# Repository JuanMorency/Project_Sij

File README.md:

# Project_Sij
Complete 600 mm Frame Drone Electrical and Sotware Design using:

- Atmega2560
- MPU9255
- 4 channel RF receiver
- Flycopter 30A BH-heli motor controllers
- WS2812B LED strips
- Madgwick Sensor Fusion

PCB was designed using Eagle. 

Second iteration of the board with much more processing power for sensor fusion should be considered to continue this project

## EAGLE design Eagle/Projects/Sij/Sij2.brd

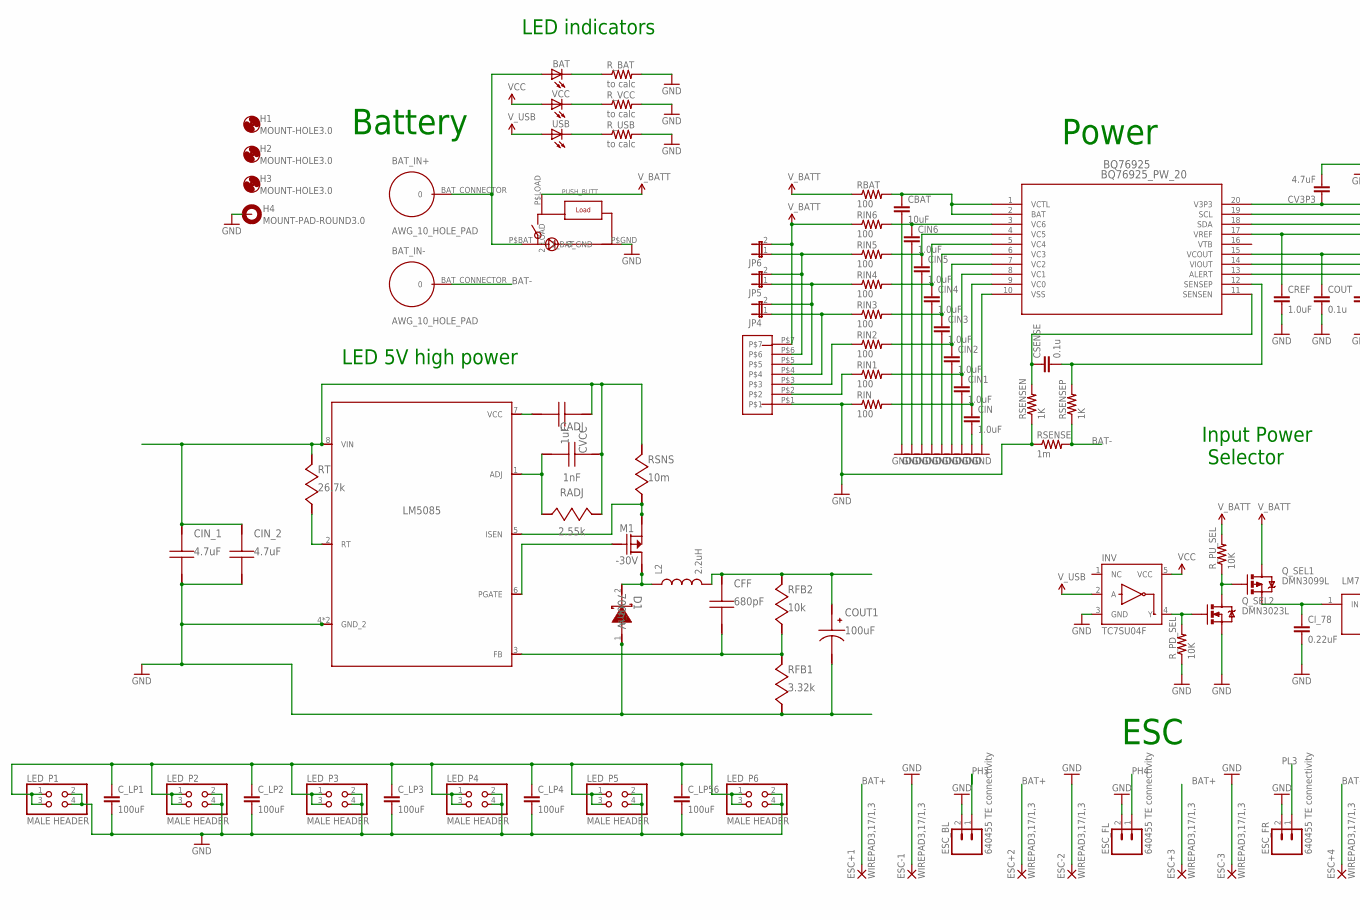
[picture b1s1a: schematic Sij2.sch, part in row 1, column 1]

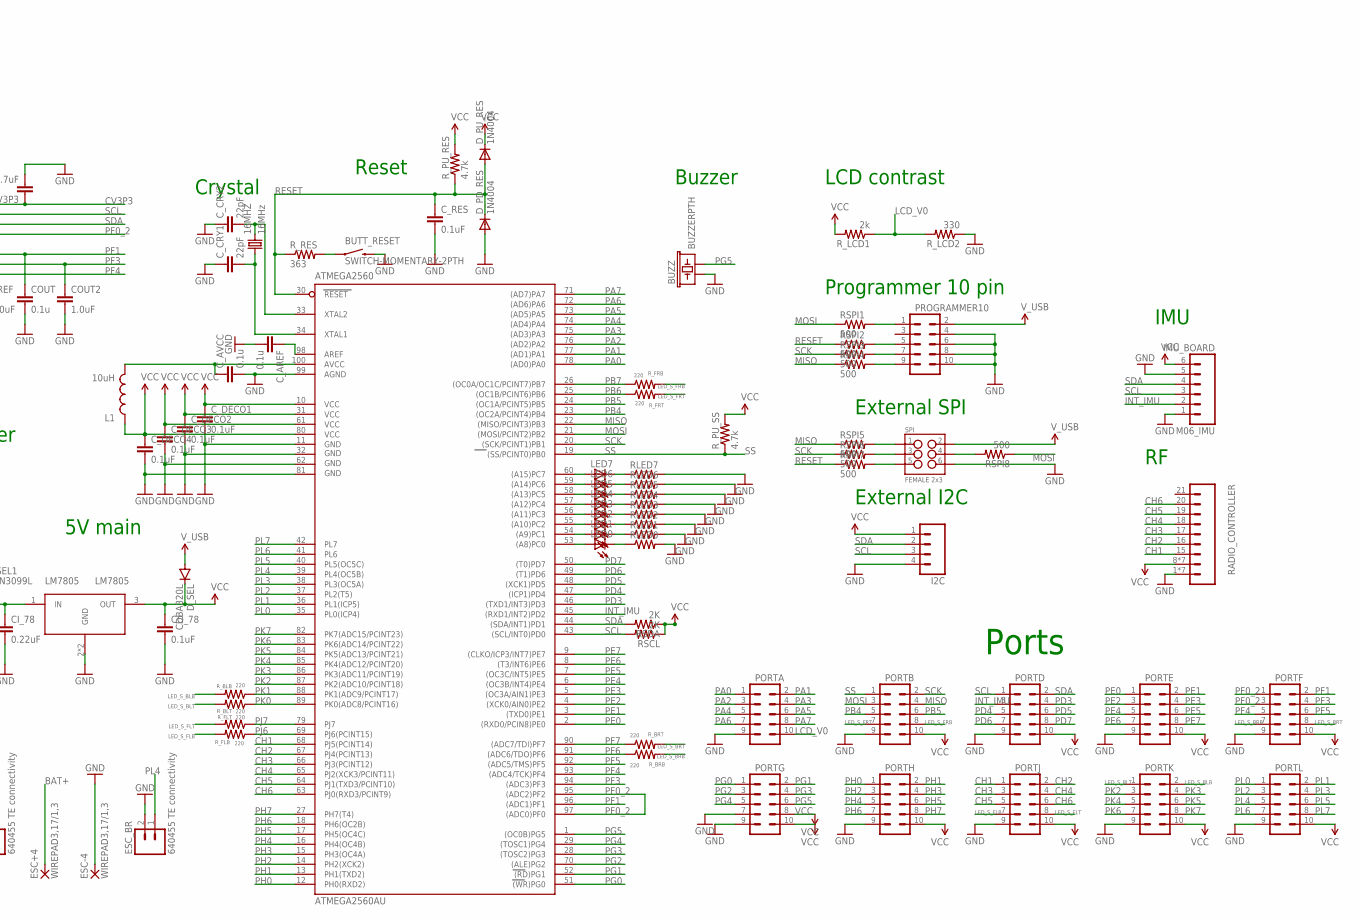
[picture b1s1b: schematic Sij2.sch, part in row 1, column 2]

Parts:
16MHZ: 16MHz; HC49US
ATMEGA2560: ATMEGA2560AU; TQFP100
BAT: LEDCHIPLED_0805; CHIPLED_0805
BAT-MONIT: 7_PIN_JST-XH
BAT_IN+: AWG_10_HOLE_PAD; AWG10_HOLE_PAD
BAT_IN-: AWG_10_HOLE_PAD; AWG10_HOLE_PAD
BQ76925: BQ76925_PW_20; PW20
BUTT_RESET: SWITCH-MOMENTARY-2PTH; TACTILE-PTH
BUZZ: BUZZERPTH; BUZZER-12MM
CADJ: 1nF; 0201
CBAT: 10uF; 0805
CFF: 680pF; 0603
CIN, CIN1, CIN2, CIN3, CIN4, CIN5, CIN6: 1.0uF; 0603-CAP
CIN_1, CIN_2: 4.7uF; 0805
CI_78: 0.22uF; 0603-CAP
COUT: 0.1u; 0603-CAP
COUT1: 100uF; CAPSMT_6_A09
COUT2: 1.0uF; 0603-CAP
CO_78: 0.1uF; 0603-CAP
CREF: 1.0uF; 0603-CAP
CSENSE: 0.1u; 0603-CAP
CV3P3: 4.7uF; 0603-CAP
CVCC: 1uF; 0603
C_AREF: 0.1u; 0603-CAP
C_AVCC: 0.1u; 0603-CAP
C_CRY1, C_CRY2: 22pF; 0603-CAP
C_DECO1, C_DECO2, C_DECO3, C_DECO4: 0.1uF; 0603-CAP
C_LP1, C_LP2, C_LP3, C_LP4, C_LP56: 100uF; 1206
C_RES: 0.1uF; 0603-CAP
D1: 700mV; DDPAK
D_PD_RES: 1N4004; DO41-10
D_PU_RES: 1N4004; DO41-10
D_SEL: CDBA320L; SMA-DIODE_ALT
ESC+1, ESC+2, ESC+3, ESC+4: WIREPAD3,17/1,3; 3,17/1,3
ESC-1, ESC-2, ESC-3, ESC-4: WIREPAD3,17/1,3; 3,17/1,3
ESC_BL: 640455 TE connectivity; 1X02
ESC_BR: 640455 TE connectivity; 1X02
ESC_FL: 640455 TE connectivity; 1X02
ESC_FR: 640455 TE connectivity; 1X02
H1, H2, H3: MOUNT-HOLE3.0; 3,0
H4: MOUNT-PAD-ROUND3.0; 3,0-PAD
I2C: M041X04_NO_SILK; 1X04_NO_SILK
IMU_BOARD: M06_IMU; 1X06_LONGPADS
INV: TC7SU04F; SOT23-5
JP4, JP5, JP6: JUMPER-2PTH; 1X02
L1: 10uH; 0805
L2: 2.2uH; MGV0605
LED0, LED1, LED2, LED3, LED4, LED5, LED6, LED7: LEDCHIPLED_0805; CHIPLED_0805
LED_P1, LED_P2, LED_P3, LED_P4, LED_P5, LED_P6: MALE HEADER; 2X02
LM5085: LM5085MY/NOPB; MUY08A
LM7805: LM7805; KTT3
M1: -30V; POWERPAK_SO-8
PORTA: M05X2PTH; AVR_ICSP
PORTB: M05X2PTH; AVR_ICSP
PORTD: M05X2PTH; AVR_ICSP
PORTE: M05X2PTH; AVR_ICSP
PORTF: M05X2PTH; AVR_ICSP
PORTG: M05X2PTH; AVR_ICSP
PORTH: M05X2PTH; AVR_ICSP
PORTJ: M05X2PTH; AVR_ICSP
PORTK: M05X2PTH; AVR_ICSP
PORTL: M05X2PTH; AVR_ICSP
PROGRAMMER10: M05X2PTH; AVR_ICSP
PUSH_BUTT: PUSH_BUTTON
Q_SEL1: DMN3099L; SOT23-3
Q_SEL2: DMN3023L; SOT23-3
RADIO_CONTROLLER: RF_CONTROL_3X7_CON; 3X07
RADJ: 2.55k; 0603
RBAT: 100; R0603
RFB1: 3.32k; 0603
RFB2: 10k; 0603
RIN, RIN1, RIN2, RIN3, RIN4, RIN5, RIN6: 100; R0603
RLED0, RLED1, RLED2, RLED3, RLED4, RLED5, RLED6, RLED7: R-US_R0603; R0603
RSCL: 2K; R0603
RSDA: 2K; R0603
RSENSE: 1m; R1206
RSENSEN: 1K; R0603
RSENSEP: 1K; R0603
RSNS: 10m; 1206
RSPI1, RSPI2, RSPI3, RSPI4, RSPI5, RSPI6, RSPI7, RSPI8: 500; R0603
RT: 26.7k; 0603
R_BAT: to calc; R0603
R_BLB: 220; R0603
R_BLT: 220; R0603
R_BRB: 220; R0603
R_BRT: 220; R0603
R_FLB: 220; R0603
R_FLT: 220; R0603
R_FRB: 220; R0603
R_FRT: 220; R0603
R_LCD1: 2k; R0603
R_LCD2: 330; R0603
R_PD_SEL: 10K; R0603
R_PU_RES: 4.7k; R0603
R_PU_SEL: 10K; R0603
R_PU_SS: 4.7k; R0603
R_RES: 363; R0603
R_USB: to calc; R0603
R_VCC: to calc; R0603
SPI: FEMALE 2x3; 2X3
USB: LEDCHIPLED_0805; CHIPLED_0805
VCC: LEDCHIPLED_0805; CHIPLED_0805

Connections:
9_5085: D1.2 (K), L2.P$1 (1), M1.5 (DRAIN_2), M1.6 (DRAIN_2), M1.7 (DRAIN_2), M1.8 (DRAIN_2), M1.9 (DRAIN_2)
ADJ_1085: CADJ.2, LM5085.1 (ADJ), RADJ.2
BAT+: BAT.A, BAT_IN+.BAT_CONNECTOR, ESC+1.1, ESC+2.1, ESC+3.1, ESC+4.1, PUSH_BUTT.P$BAT (1_BAT)
BAT-: BAT_IN-.BAT_CONNECTOR, RSENSE.2, RSENSEP.1
CH1: ATMEGA2560.68 (PJ5(PCINT14)), PORTJ.1, RADIO_CONTROLLER.15 (1)
CH2: ATMEGA2560.67 (PJ4(PCINT13)), PORTJ.2, RADIO_CONTROLLER.16 (2)
CH3: ATMEGA2560.66 (PJ3(PCINT12)), PORTJ.3, RADIO_CONTROLLER.17 (3)
CH4: ATMEGA2560.65 (PJ2(XCK3/PCINT11)), PORTJ.4, RADIO_CONTROLLER.18 (4)
CH5: ATMEGA2560.64 (PJ1(TXD3/PCINT10)), PORTJ.5, RADIO_CONTROLLER.19 (5)
CH6: ATMEGA2560.63 (PJ0(RXD3/PCINT9)), PORTJ.6, RADIO_CONTROLLER.20 (6)
CV3P3: BQ76925.20 (V3P3), CV3P3.1
FB_5085: CFF.2, LM5085.3 (FB), RFB1.1, RFB2.2
GND: ATMEGA2560.11 (GND), ATMEGA2560.32 (GND1), ATMEGA2560.62 (GND2), ATMEGA2560.81 (GND3), ATMEGA2560.99 (AGND), BAT-MONIT.P$1, BQ76925.10 (VSS), BUTT_RESET.3 (2), BUTT_RESET.4 (2), BUZZ.+ (1), CBAT.2, CIN.2, CIN1.2, CIN2.2, CIN3.2, CIN4.2, CIN5.2, CIN6.2, CIN_1.2, CIN_2.2, CI_78.2, COUT.2, COUT1.2 (-), COUT2.2, CO_78.2, CREF.2, CV3P3.2, C_AREF.2, C_AVCC.2, C_CRY1.1, C_CRY2.1, C_DECO1.2, C_DECO2.2, C_DECO3.2, C_DECO4.2, C_LP1.2, C_LP2.2, C_LP3.2, C_LP4.2, C_LP56.2, C_RES.2, D1.1 (A_2), D_PD_RES.A, ESC-1.1, ESC-2.1, ESC-3.1, ESC-4.1, ESC_BL.2, ESC_BR.2, ESC_FL.2, ESC_FR.2, H4.B3,0, I2C.4, IMU_BOARD.1, IMU_BOARD.5, INV.3 (GND), LED_P1.2, LED_P1.4, LED_P2.2, LED_P2.4, LED_P3.2, LED_P3.4, LED_P4.2, LED_P4.4, LED_P5.2, LED_P5.4, LED_P6.2, LED_P6.4, LM5085.4 (GND_2), LM5085.9 (GND_2), LM7805.2 (GND), LM7805.4 (GND), PORTA.9, PORTB.9, PORTD.9, PORTE.9, PORTF.9, PORTG.7, PORTG.9, PORTH.9, PORTJ.9, PORTK.9, PORTL.9, PROGRAMMER10.4, PROGRAMMER10.6, PROGRAMMER10.8, PROGRAMMER10.10, PUSH_BUTT.P$GND (3_GND), Q_SEL2.2 (S), RADIO_CONTROLLER.1 (GND), RADIO_CONTROLLER.2 (GND), RADIO_CONTROLLER.3 (GND), RADIO_CONTROLLER.4 (GND), RADIO_CONTROLLER.5 (GND), RADIO_CONTROLLER.6 (GND), RADIO_CONTROLLER.7 (GND), RFB1.2, RIN.1, RLED0.2, RLED1.2, RLED2.2, RLED3.2, RLED4.2, RLED5.2, RLED6.2, RLED7.2, RSENSE.1, RSENSEN.1, R_BAT.2, R_LCD2.1, R_PD_SEL.1, R_USB.2, R_VCC.2, SPI.6
INT_IMU: ATMEGA2560.45 ((RXD1/INT2)PD2), IMU_BOARD.2, PORTD.3
ISEN_5085: LM5085.5 (ISEN), M1.1 (SOURCE_2), M1.2 (SOURCE_2), M1.3 (SOURCE_2), RSNS.2
LCD_V0: PORTA.10, R_LCD1.1, R_LCD2.2
LED_S_BLB: PORTK.2, R_BLB.2
LED_S_BLT: PORTK.1, R_BLT.2
LED_S_BRB: PORTF.7, R_BRB.2
LED_S_BRT: PORTF.8, R_BRT.2
LED_S_FLB: PORTJ.7, R_FLB.2
LED_S_FLT: PORTJ.8, R_FLT.2
LED_S_FRB: PORTB.8, R_FRB.2
LED_S_FRT: PORTB.7, R_FRT.2
MISO: ATMEGA2560.22 ((MISO/PCINT3)PB3), PORTB.4, RSPI4.1, RSPI5.1
MOSI: ATMEGA2560.21 ((MOSI/PCINT2)PB2), PORTB.3, RSPI1.1, RSPI8.1
unnamed: PROGRAMMER10.7, RSPI3.2
unnamed: PROGRAMMER10.1, RSPI1.2
unnamed: PROGRAMMER10.9, RSPI4.2
unnamed: CI_78.1, LM7805.1 (IN), Q_SEL1.2 (S)
unnamed: ATMEGA2560.100 (AVCC), C_AVCC.1, L1.2
unnamed: 16MHZ.1, ATMEGA2560.34 (XTAL1), C_CRY1.2
unnamed: BQ76925.6 (VC3), CIN3.1, RIN3.2
unnamed: BQ76925.1 (VCTL), BQ76925.2 (BAT), CBAT.1, RBAT.2
unnamed: BQ76925.7 (VC2), CIN2.1, RIN2.2
unnamed: BQ76925.8 (VC1), CIN1.1, RIN1.2
unnamed: BQ76925.9 (VC0), CIN.1, RIN.2
unnamed: BQ76925.5 (VC4), CIN4.1, RIN4.2
unnamed: INV.4 (Y), Q_SEL2.1 (G), R_PD_SEL.2
unnamed: ATMEGA2560.60 ((A15)PC7), LED7.A
unnamed: BQ76925.11 (SENSEN), CSENSE.1, RSENSEN.2
unnamed: BQ76925.12 (SENSEP), CSENSE.2, RSENSEP.2
unnamed: BQ76925.3 (VC6), CIN6.1, RIN6.2
unnamed: BQ76925.4 (VC5), CIN5.1, RIN5.2
unnamed: ATMEGA2560.59 ((A14)PC6), LED6.A
unnamed: ATMEGA2560.58 ((A13)PC5), LED5.A
unnamed: ATMEGA2560.57 ((A12)PC4), LED4.A
unnamed: ATMEGA2560.56 ((A11)PC3), LED3.A
unnamed: BAT-MONIT.P$2, RIN1.1
unnamed: RSPI8.2, SPI.4
unnamed: ATMEGA2560.55 ((A10)PC2), LED2.A
unnamed: ATMEGA2560.54 ((A9)PC1), LED1.A
unnamed: BAT-MONIT.P$3, RIN2.1
unnamed: BAT-MONIT.P$4, JP4.1, RIN3.1
unnamed: BAT-MONIT.P$5, JP4.2, JP5.1, RIN4.1
unnamed: BAT-MONIT.P$6, JP5.2, JP6.1, RIN5.1
unnamed: ATMEGA2560.53 ((A8)PC0), LED0.A
unnamed: BUTT_RESET.1, BUTT_RESET.2 (1), R_RES.2
unnamed: R_USB.1, USB.C
unnamed: 16MHZ.2, ATMEGA2560.33 (XTAL2), C_CRY2.2
unnamed: Q_SEL1.1 (G), Q_SEL2.3 (D), R_PU_SEL.1
unnamed: R_VCC.1, VCC.C
unnamed: LED7.C, RLED7.1
unnamed: LED6.C, RLED6.1
unnamed: LED5.C, RLED5.1
unnamed: RSPI6.2, SPI.3
unnamed: LED4.C, RLED4.1
unnamed: LED3.C, RLED3.1
unnamed: LED2.C, RLED2.1
unnamed: LED1.C, RLED1.1
unnamed: LED0.C, RLED0.1
unnamed: BAT.C, R_BAT.1
unnamed: RSPI5.2, SPI.1
unnamed: PROGRAMMER10.5, RSPI2.2
unnamed: ATMEGA2560.98 (AREF), C_AREF.1
unnamed: RSPI7.2, SPI.5
PA0: ATMEGA2560.78 ((AD0)PA0), PORTA.1
PA1: ATMEGA2560.77 ((AD1)PA1), PORTA.2
PA2: ATMEGA2560.76 ((AD2)PA2), PORTA.3
PA3: ATMEGA2560.75 ((AD3)PA3), PORTA.4
PA4: ATMEGA2560.74 ((AD4)PA4), PORTA.5
PA5: ATMEGA2560.73 ((AD5)PA5), PORTA.6
PA6: ATMEGA2560.72 ((AD6)PA6), PORTA.7
PA7: ATMEGA2560.71 ((AD7)PA7), PORTA.8
PB4: ATMEGA2560.23 ((OC2A/PCINT4)PB4), PORTB.5
PB5: ATMEGA2560.24 ((OC1A/PCINT5)PB5), PORTB.6
PB6: ATMEGA2560.25 ((OC1B/PCINT6)PB6), R_FRT.1
PB7: ATMEGA2560.26 ((OC0A/OC1C/PCINT7)PB7), R_FRB.1
PD3: ATMEGA2560.46 ((TXD1/INT3)PD3), PORTD.4
PD4: ATMEGA2560.47 ((ICP1)PD4), PORTD.5
PD5: ATMEGA2560.48 ((XCK1)PD5), PORTD.6
PD6: ATMEGA2560.49 ((T1)PD6), PORTD.7
PD7: ATMEGA2560.50 ((T0)PD7), PORTD.8
PE0: ATMEGA2560.2 ((RXD0/PCIN8)PE0), PORTE.1
PE1: ATMEGA2560.3 ((TXD0)PE1), PORTE.2
PE2: ATMEGA2560.4 ((XCK0/AIN0)PE2), PORTE.3
PE3: ATMEGA2560.5 ((OC3A/AIN1)PE3), PORTE.4
PE4: ATMEGA2560.6 ((OC3B/INT4)PE4), PORTE.5
PE5: ATMEGA2560.7 ((OC3C/INT5)PE5), PORTE.6
PE6: ATMEGA2560.8 ((T3/INT6)PE6), PORTE.7
PE7: ATMEGA2560.9 ((CLKO/ICP3/INT7)PE7), PORTE.8
PF0_2: ATMEGA2560.95 ((ADC2)PF2), ATMEGA2560.97 ((ADC0)PF0), BQ76925.17 (VREF), CREF.1, PORTF.1, PORTF.3
PF1: ATMEGA2560.96 ((ADC1)PF1), BQ76925.15 (VCOUT), COUT.1, PORTF.2
PF3: ATMEGA2560.94 ((ADC3)PF3), BQ76925.14 (VIOUT), COUT2.1, PORTF.4
PF4: ATMEGA2560.93 ((ADC4/TCK)PF4), BQ76925.13 (ALERT), PORTF.5
PF5: ATMEGA2560.92 ((ADC5/TMS)PF5), PORTF.6
PF6: ATMEGA2560.91 ((ADC6/TDO)PF6), R_BRB.1
PF7: ATMEGA2560.90 ((ADC7/TDI)PF7), R_BRT.1
PG0: ATMEGA2560.51 ((WR)PG0), PORTG.1
PG1: ATMEGA2560.52 ((RD)PG1), PORTG.2
PG2: ATMEGA2560.70 ((ALE)PG2), PORTG.3
PG3: ATMEGA2560.28 ((TOSC2)PG3), PORTG.4
PG4: ATMEGA2560.29 ((TOSC1)PG4), PORTG.5
PG5: ATMEGA2560.1 ((OC0B)PG5), BUZZ.- (2), PORTG.6
PGATE_5085: LM5085.6 (PGATE), M1.4 (GATE)
PH0: ATMEGA2560.12 (PH0(RXD2)), PORTH.1
PH1: ATMEGA2560.13 (PH1(TXD2)), PORTH.2
PH2: ATMEGA2560.14 (PH2(XCK2)), PORTH.3
PH3: ATMEGA2560.15 (PH3(OC4A)), ESC_BL.1, PORTH.4
PH4: ATMEGA2560.16 (PH4(OC4B)), ESC_FL.1, PORTH.5
PH5: ATMEGA2560.17 (PH5(OC4C)), PORTH.6
PH6: ATMEGA2560.18 (PH6(OC2B)), PORTH.7
PH7: ATMEGA2560.27 (PH7(T4)), PORTH.8
PJ6: ATMEGA2560.69 (PJ6(PCINT15)), R_FLB.1
PJ7: ATMEGA2560.79 (PJ7), R_FLT.1
PK0: ATMEGA2560.89 (PK0(ADC8/PCINT16)), R_BLT.1
PK1: ATMEGA2560.88 (PK1(ADC9/PCINT17)), R_BLB.1
PK2: ATMEGA2560.87 (PK2(ADC10/PCINT18)), PORTK.3
PK3: ATMEGA2560.86 (PK3(ADC11/PCINT19)), PORTK.4
PK4: ATMEGA2560.85 (PK4(ADC12/PCINT20)), PORTK.5
PK5: ATMEGA2560.84 (PK5(ADC13/PCINT21)), PORTK.6
PK6: ATMEGA2560.83 (PK6(ADC14/PCINT22)), PORTK.7
PK7: ATMEGA2560.82 (PK7(ADC15/PCINT23)), PORTK.8
PL0: ATMEGA2560.35 (PL0(ICP4)), PORTL.1
PL1: ATMEGA2560.36 (PL1(ICP5)), PORTL.2
PL2: ATMEGA2560.37 (PL2(T5)), PORTL.3
PL3: ATMEGA2560.38 (PL3(OC5A)), ESC_FR.1, PORTL.4
PL4: ATMEGA2560.39 (PL4(OC5B)), ESC_BR.1, PORTL.5
PL5: ATMEGA2560.40 (PL5(OC5C)), PORTL.6
PL6: ATMEGA2560.41 (PL6), PORTL.7
PL7: ATMEGA2560.42 (PL7), PORTL.8
RESET: ATMEGA2560.30 (RESET), C_RES.1, D_PD_RES.C, D_PU_RES.A, RSPI2.1, RSPI7.1, R_PU_RES.1, R_RES.1
RT_5085: LM5085.2 (RT), RT.2
SCK: ATMEGA2560.20 ((SCK/PCINT1)PB1), PORTB.2, RSPI3.1, RSPI6.1
SCL: ATMEGA2560.43 ((SCL/INT0)PD0), BQ76925.19 (SCL), I2C.3, IMU_BOARD.3, PORTD.1, RSCL.2
SDA: ATMEGA2560.44 ((SDA/INT1)PD1), BQ76925.18 (SDA), I2C.2, IMU_BOARD.4, PORTD.2, RSDA.2
SS: ATMEGA2560.19 ((SS/PCINT0)PB0), PORTB.1, R_PU_SS.1
VCC: ATMEGA2560.10 (VCC), ATMEGA2560.31 (VCC1), ATMEGA2560.61 (VCC2), ATMEGA2560.80 (VCC3), CO_78.1, C_DECO1.1, C_DECO2.1, C_DECO3.1, C_DECO4.1, D_PU_RES.C, D_SEL.C, I2C.1, IMU_BOARD.6, INV.5 (VCC), L1.1, LM7805.3 (OUT), PORTB.10, PORTD.10, PORTE.10, PORTF.10, PORTG.8, PORTG.10, PORTH.10, PORTJ.10, PORTK.10, PORTL.10, RADIO_CONTROLLER.8 (5V), RADIO_CONTROLLER.9 (5V), RADIO_CONTROLLER.10 (5V), RADIO_CONTROLLER.11 (5V), RADIO_CONTROLLER.12 (5V), RADIO_CONTROLLER.13 (5V), RADIO_CONTROLLER.14 (5V), RSCL.1, RSDA.1, R_LCD1.2, R_PU_RES.2, R_PU_SS.2, VCC.A
VCC_1085: CVCC.2, LM5085.7 (VCC)
VOUT_5085: CFF.1, COUT1.1 (+), C_LP1.1, C_LP2.1, C_LP3.1, C_LP4.1, C_LP56.1, L2.P$2 (2), LED_P1.1, LED_P1.3, LED_P2.1, LED_P2.3, LED_P3.1, LED_P3.3, LED_P4.1, LED_P4.3, LED_P5.1, LED_P5.3, LED_P6.1, LED_P6.3, RFB2.1
V_BATT: BAT-MONIT.P$7, CADJ.1, CIN_1.1, CIN_2.1, CVCC.1, JP6.2, LM5085.8 (VIN), PUSH_BUTT.P$LOAD (2_LOAD), Q_SEL1.3 (D), RADJ.1, RBAT.1, RIN6.1, RSNS.1, RT.1, R_PU_SEL.2
V_USB: D_SEL.A, INV.2 (A), PROGRAMMER10.2, SPI.2, USB.A

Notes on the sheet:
ESC
Power
Battery
LED indicators
IMU
Programmer 10 pin
Reset
Crystal
External SPI
External I2C
5V main
LED 5V high power
Input Power Selector
Ports
Buzzer
LCD contrast

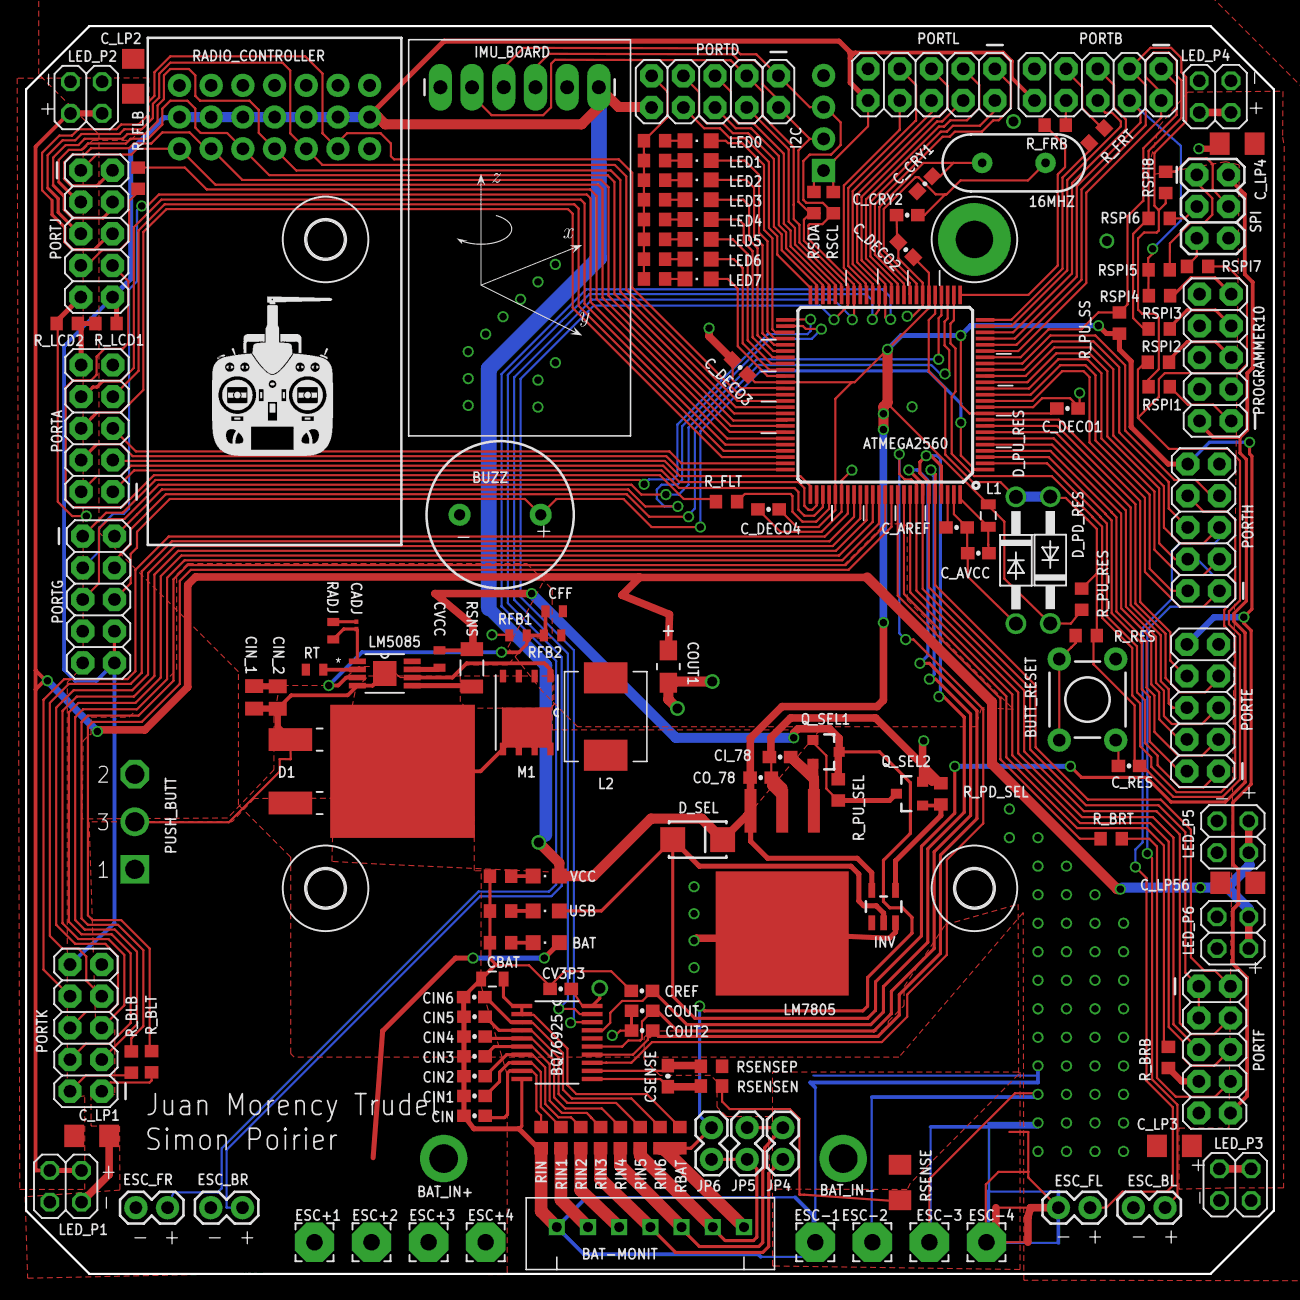
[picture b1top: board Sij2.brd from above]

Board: 2 copper layers, 100.0 x 100.0 mm, 159 parts (0 on the bottom side), 152 nets.

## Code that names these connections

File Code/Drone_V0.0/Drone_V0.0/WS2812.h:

/**
  ******************************************************************************
	* File Name         : WS2812.h
	* Description       : header for WS2812.cpp
	* Author			: Matthias Riegler, Juan Morency Trudel (Adaptation)
	* Version           : 2.1
	* Date				: September 6, 2014
	* License			: GNU GPL v2 (see License.txt)
	* Comment			: Mar 07 2014: Added Arduino and C++ Library
						  September 6, 2014:	Added option to switch between most popular color orders
						  (RGB, GRB, and BRG) --  Windell H. Oskay
	
  ******************************************************************************
  */

#ifndef WS2812_H_
#define WS2812_H_

#include <avr/interrupt.h>
#include <avr/io.h>
#ifndef F_CPU
#define  F_CPU 16000000UL
#endif
#include <util/delay.h>
#include <stdint.h>

#define FRT 0	// PB6
#define FRB 1	// PB7
#define FLT 2	// PJ7
#define FLB 3	// PJ6
#define BRT 4	// PF7
#define BRB 5	// PF6
#define BLT 6	// PK0
#define BLB 7	// PK1

extern bool ws2812Initialized;

void initWS2812(void);

/*
dim_curve 'lookup table' to compensate for the nonlinearity of human vision.
Used in the getRGB function on saturation and brightness to make 'dimming' look more natural.
Exponential function used to create values below :
x from 0 - 255 : y = round(pow( 2.0, x+64/40.0) - 1)
*/

//comment this if HSV is not used
#define USE_HSV

#ifdef USE_HSV
const uint8_t dim_curve[] = {
	0, 1, 1, 2, 2, 2, 2, 2, 2, 3, 3, 3, 3, 3, 3, 3,
	3, 3, 3, 3, 3, 3, 3, 4, 4, 4, 4, 4, 4, 4, 4, 4,
	4, 4, 4, 5, 5, 5, 5, 5, 5, 5, 5, 5, 5, 6, 6, 6,
	6, 6, 6, 6, 6, 7, 7, 7, 7, 7, 7, 7, 8, 8, 8, 8,
	8, 8, 9, 9, 9, 9, 9, 9, 10, 10, 10, 10, 10, 11, 11, 11,
	11, 11, 12, 12, 12, 12, 12, 13, 13, 13, 13, 14, 14, 14, 14, 15,
	15, 15, 16, 16, 16, 16, 17, 17, 17, 18, 18, 18, 19, 19, 19, 20,
	20, 20, 21, 21, 22, 22, 22, 23, 23, 24, 24, 25, 25, 25, 26, 26,
	27, 27, 28, 28, 29, 29, 30, 30, 31, 32, 32, 33, 33, 34, 35, 35,
	36, 36, 37, 38, 38, 39, 40, 40, 41, 42, 43, 43, 44, 45, 46, 47,
	48, 48, 49, 50, 51, 52, 53, 54, 55, 56, 57, 58, 59, 60, 61, 62,
	63, 64, 65, 66, 68, 69, 70, 71, 73, 74, 75, 76, 78, 79, 81, 82,
	83, 85, 86, 88, 90, 91, 93, 94, 96, 98, 99, 101, 103, 105, 107, 109,
	110, 112, 114, 116, 118, 121, 123, 125, 127, 129, 132, 134, 136, 139, 141, 144,
	146, 149, 151, 154, 157, 159, 162, 165, 168, 171, 174, 177, 180, 183, 186, 190,
	193, 196, 200, 203, 207, 211, 214, 218, 222, 226, 230, 234, 238, 242, 248, 255,
};
#endif

// If you want to use the setColorOrder functions, enable this line
#define RGB_ORDER_ON_RUNTIME

#ifdef RGB_ORDER_ON_RUNTIME	
	#define OFFSET_R(r) r+offsetRed
	#define OFFSET_G(g) g+offsetGreen
	#define OFFSET_B(b) b+offsetBlue
#else
// CHANGE YOUR STATIC RGB ORDER HERE
	#define OFFSET_R(r) r+1
	#define OFFSET_G(g) g	
	#define OFFSET_B(b) b+2	
#endif

//Macro _BV byte value
#define _BV(bit) (1 << (bit))



struct cRGB { 
	uint8_t g; 
	uint8_t r; 
	uint8_t b;


#ifdef USE_HSV
	void SetHSV(int hue, uint8_t sat, uint8_t val) {
		/* convert hue, saturation and brightness ( HSB/HSV ) to RGB
		The dim_curve is used only on brightness/value and on saturation (inverted).
		This looks the most natural.
		*/

		val = dim_curve[val];
		sat = 255 - dim_curve[255 - sat];

		int base;

		if (sat == 0) { // Acromatic color (gray). Hue doesn't mind.
			r = val;
			g = val;
			b = val;
		}
		else  {
			base = ((255 - sat) * val) >> 8;

			switch (hue / 60) {
			case 0:
				r = val;
				g = (((val - base)*hue) / 60) + base;
				b = base;
				break;

			case 1:
				r = (((val - base)*(60 - (hue % 60))) / 60) + base;
				g = val;
				b = base;
				break;

			case 2:
				r = base;
				g = val;
				b = (((val - base)*(hue % 60)) / 60) + base;
				break;

			case 3:
				r = base;
				g = (((val - base)*(60 - (hue % 60))) / 60) + base;
				b = val;
				break;

			case 4:
				r = (((val - base)*(hue % 60)) / 60) + base;
				g = base;
				b = val;
				break;

			case 5:
				r = val;
				g = base;
				b = (((val - base)*(60 - (hue % 60))) / 60) + base;
				break;
			}			
		}
	}
#endif	
};


class WS2812 {
	public: 
		WS2812(uint16_t num_led, uint8_t stripPosition);
		~WS2812();
	
		void setOutput(volatile uint8_t *port, volatile uint8_t *ddr, uint8_t pin);
		void setAsOutput();
		cRGB get_crgb_at(uint16_t index);
		uint8_t set_crgb_at(uint16_t index, cRGB px_value);
		uint8_t set_subpixel_at(uint16_t index, uint8_t offset, uint8_t px_value);
		void sync();
		void reset();
		
	#ifdef RGB_ORDER_ON_RUNTIME	
		void setColorOrderRGB();
		void setColorOrderGRB();
		void setColorOrderBRG();
	#endif

	private:
		uint16_t count_led;
		uint8_t *pixels;

	#ifdef RGB_ORDER_ON_RUNTIME	
		uint8_t offsetRed;
		uint8_t offsetGreen;
		uint8_t offsetBlue;
	#endif	

		void ws2812_sendarray_mask(uint8_t *array,uint16_t length, uint8_t pinmask,uint8_t *port, uint8_t *portreg);
		volatile uint8_t *ws2812_port;
		volatile uint8_t *ws2812_port_reg;
		uint8_t pinMask;
		volatile uint8_t stripPosition; 
};


#endif /* WS2812_H_ */

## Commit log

2016-07-02 Create Liste de materiel
2016-07-02 Create Microcontrolleur
2016-07-02 Update Liste de materiel
2016-07-02 Create Ressources web
2016-07-02 Create Frame
2016-07-02 Create Moteurs
2016-07-02 Update Moteurs
2016-07-02 Update Ressources web
2016-07-04 Update Microcontrolleur
2016-07-07 Update Liste de materiel
    LCD
2016-07-07 Update Microcontrolleur
    comparaison AVR vs Microchip
2016-07-08 Create Radio Controller
2016-07-08 Update Radio Controller
2016-07-09 docuentation
2016-07-09 oups
2016-07-09 enlevé Isabelle
2016-07-10 Create Battery
2016-07-10 J'ai mis un peu d'ordre et j'ai rajouté de la documentation
2016-07-10 test pour commit
2016-07-26 Create Matériel circuit
    crystal trouvé
2016-07-31 test
2016-07-31 allo j'ai change les noms
2016-07-31 bibliothèque eagle+script+projet
2016-07-31 ajouté liste de magasinage Abra
2016-07-31 exemple code RC
2016-07-31 ajouté un fichier text avec le hardware qu'on utilise pour le power Management
2016-08-01 ajouté ma custom bibliotheque avec les trucs de TI
2016-08-01 Ajouté le gitignore pour des fichiers inutiles
2016-08-01 le vrai commit avec le gitignore
2016-08-01 ajouté des pièces pour digikey
2016-08-02 ajouté des bibliothèques de composantes, modifié beaucoup le schematic du pcb et ajouté des listes d'épicerie
2016-08-03 commandé
2016-08-03 ajusté les listes d'épicerie
2016-08-03 modifié le TODO
2016-08-03 juste souligné quelques trucs dans la documentation
2016-08-03 ISP OK (incluant SS)
2016-08-04 annoté documentation
2016-08-05 joué avec le schematic et la commande digikey
2016-08-05 documentation du IMU
2016-08-05 fini le schematic préliminaire+bibliothèques de partie+documentation
2016-08-05 doc RC update
2016-08-07 listes matériel
2016-08-08 quelques ports ajoutés
2016-08-15 quelques ports
2016-08-15 creation dossier pour le code
2016-08-15 presque rien
2016-08-25 ajouté un project pour tester ta configuration qui fait alterner le port D entre 0 et 5V, ajouté de la documentation
2016-08-25 ajouté la photo des connexions pour le board sans crystal
2016-08-25 J'ai travaillé sur le schematic du PCB. Pas mal final
2016-08-26 joué un peu avec le layout
2016-08-26 schematics PWM changé
2016-08-26 fichiers pour code ESC créés
2016-08-28 registres PWM initialisés
2016-08-31 joué un peu avec le code PWM
2016-09-03 Ajouté les fonctionnlités d'un simple interrupt
2016-09-03 commencé le code pourlire le pwm du Radio controller et j'ai ajouté du code pour le LCD
2016-09-04 le LCD fonctionne plus d'autres modifications mineurs
2016-09-05 radio controlleur fonctionne presque
2016-09-05 divisé par 2 le pw et ça fontionne
2016-09-05 ménage à faire
2016-09-05 rendu le code un peu plus beau
2016-09-09 Modifié le PCB
2016-09-12 presque terminé le layout. Après genre 20h de travail acharné!
2016-09-19 PCB presque terminé
2016-11-19 Added code for I2C and IMU
2016-12-24 Ajouter le dernier eagle qui a été envoyé à la manufacture, le code pour le I2C préliminaire, le code pour le WS2812 led strip.
2016-12-24 Ajouter qulques fonctions a WS2812 + debut de documentation du code
2016-12-24 Added comments for I2C methods
2016-12-24 macro LED
2017-02-11 ajouter les interrupts,ISR et FSM pour LED, ESC, RF et LCD. J'ai aussi fait un peu de menage dans le git
2017-02-11 ajouter quelques gitignore
2017-02-14 ajouté le interrupt pour le IMU. Testé le code et semble avoir un problème quand on lit plus d'une donné sur le IMU. Vérifier le code I2C
2017-02-14 update le git ignore
2017-02-17 Tentative de regler le probleme du IMU, on recoit seulement une fois les donnees et ensuite elle ne change plus, le IMU n'update plus ses valeurs... a tester sur un arduino pour voir si le senseur es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
2017-02-24 Fixed the I2C problem, Acc/Gyr now work
2017-02-25 Added the AK8963 class and adjusted the MPU9255 one to make it better.Not fully functionnal yet
2017-02-25 Fixed the Magnetometer I2C issue. can read the address of the device right but the data seems to be off and does not change.
2017-02-25 Added BMP180 class and minor fixes. Magnetometer still broken
2017-02-26 Fixed the Magnetometer problem, works great now
2017-02-26 Added the float struct
2017-02-26 fixed the compilation error
2017-02-26 ak8963 reads values
2017-02-27 Fixed the gyroscope calibration
2017-03-01 update calculation to avoid floats on AK8973. MPU180 has good pressure value but still has a couple issue mentionned on the trello. Rearranged folders
2017-03-02 Fixed the gyro Z problem with the new hardware
2017-06-01 Added Serial testing code. This should be added to the main project. Minor modifications of the IMU code
2017-06-05 Added Serial functionnalities to DroneV0.0. Fixed the barometer. Improved the serial formating.
2017-06-11 Added but did not integrate the Madwick Sensor fusion algorithm
2017-06-11 fixed RF problems and started the Madgwick integration
2017-06-22 Fixed the Madgwick algo. Added a frequency counter for the IMU update rate. Added Euler angle conversion. Added a simple script for testing the ESCs. Other minor fixes. Removed permenantly LCD stuff.
2017-06-23 Commented methods
2017-07-06 Create new branch, added the new code for FSM, Need to work on it a little bit
2017-07-11 I2C FSM now working completely. Fixed Yaw pitch roll positive direction. Fixed magnetic offsets. Changed BMP180 to object again and implemented it for I2C FSM
2017-07-12 Added the PID controller and objects
2017-07-18 Optimized the PID and ESC controls. We can get around 200 Hz of Acc/Gyr and 100 Hz Mag update rate when the Serial is off and ESC is slowed down. This should be enough for most of the testing
2017-08-01 fixed the debug LED problems. Fixed the ESC shutdown when RF is off with the timeout. Added yaw variable to maintain yaw direction and change that variable with RF
2018-01-03 Commented remaining uncommented code
2023-04-02 Update README.md
    Added update

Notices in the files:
Eagle/Projects/Sij/Sij2.brd:
© SiJ inc
parts and their libraries:
SparkFun-Connectors: Licensing: Creative Commons ShareAlike 4.0 International - https://creativecommons.org/licenses/by-sa/4.0
